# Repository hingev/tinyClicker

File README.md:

# tinyClicker

A bodged presentation clicker based on two parts.
The transmitter is an Attiny85 and the Receiver is an STM32F103.

```
+-------------------------------------------------------+
|                                                       |
|                                        IR LED         |
|              BUT1            t85                      |
|                            +-------+     XXXX         |
|               +--+         |       +-----+XXXX        |
|      +--------+  +---------+       |     XXXX         |
|      |                     |       |                  |
|      +--------+  +---------+       |                  |
|      |        +--+         +-------+                  |
|    +---+                               +              |
|     +-+      BUT2                      |              |
|      +                                 |              |
|                            <-----------+              |
+-------------------------------------------------------+
                             |
                             |
                             |
                 +-----------+
                 |
 +---------------+---------------------------------------------+
 |                                                             |
 |  TL 1838                                                    |
 |                                                             |
 |    XXXXX                                                    |
 |    XXXXX+      +------------------------------+             |
 |    XXXXX|      |                              |   USB HID   |
 |         |      |       STM32F103              |   AS A      |
 |         +------+                              +--------->   |
 |                |                              |   KEYBOARD  |
 |                +------------------------------+             |
 |                                                             |
 |                                                             |
 |                                                             |
 +-------------------------------------------------------------+

```

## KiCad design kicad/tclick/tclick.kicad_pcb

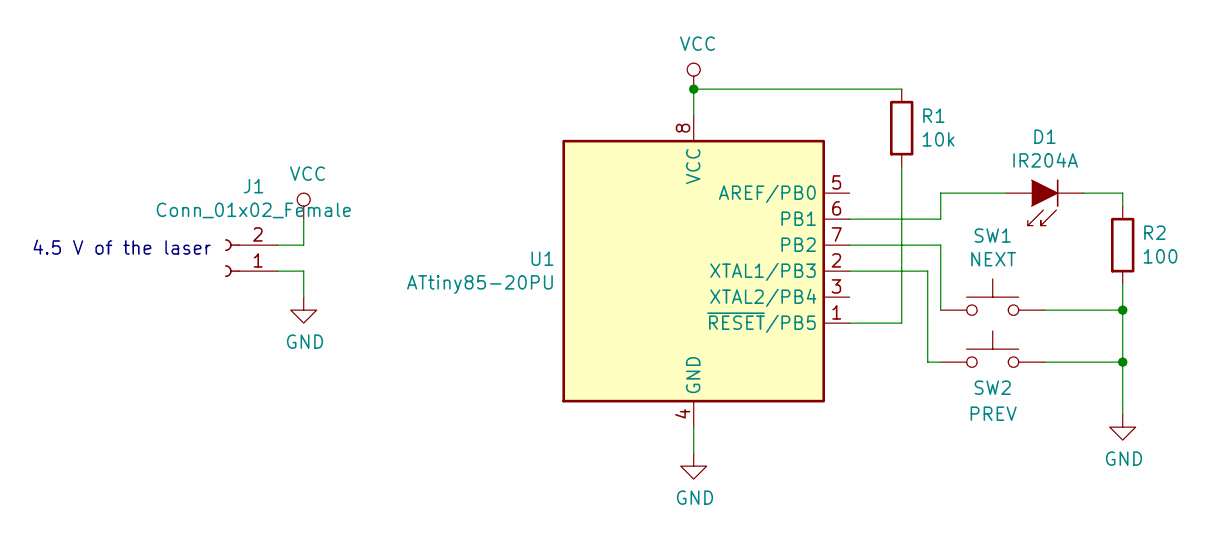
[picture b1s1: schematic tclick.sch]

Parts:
D1: IR204A; LED_D3.0mm_Horizontal_O1.27mm_Z6.0mm
J1: Conn_01x02_Female; Pin_Header_Angled_1x02_Pitch1.00mm
R1: 10k; R_0805
R2: 100; R_0805
SW1: NEXT; SW_PUSH_6mm_h4.3mm
SW2: PREV; SW_PUSH_6mm_h4.3mm
U1: ATtiny85-20PU; DIP-8_W10.16mm

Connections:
GND: J1.1, R2.2, SW1.2, SW2.2, U1.4 (GND)
unnamed: D1.1 (K), R2.1
unnamed: D1.2 (A), U1.6 (PB1)
unnamed: R1.2, U1.1 (~RESET~/PB5)
unnamed: SW1.1, U1.7 (PB2)
unnamed: SW2.1, U1.2 (XTAL1/PB3)
VCC: J1.2, R1.1, U1.8 (VCC)

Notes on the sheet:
4.5 V of the laser

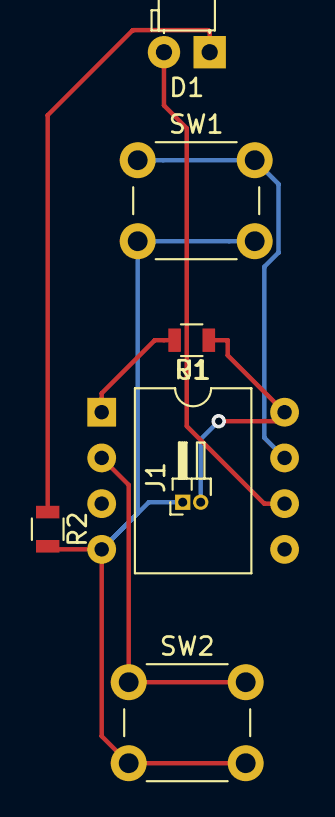
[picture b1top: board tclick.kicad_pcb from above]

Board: 2 copper layers, 7 parts (0 on the bottom side), 7 nets.

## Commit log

2019-05-23 Started working on the t85 logic
2019-05-23 add send_code function
2019-05-23 Got stuff to work
2019-05-23 add debounce
2019-05-27 Add Kicad Files
2019-05-27 Add STM code for the IR keyboard
2019-05-27 Create LICENSE
2019-05-27 Add README
